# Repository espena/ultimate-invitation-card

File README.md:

# Ultimate invitation card
Invitation card for geeks!

You will find a detailed description of this project on my blog, at [espenandersen.no/ultimate-invitation-card](https://espenandersen.no/ultimate-invitation-card/).

## Prototype

## Schematics

## Development

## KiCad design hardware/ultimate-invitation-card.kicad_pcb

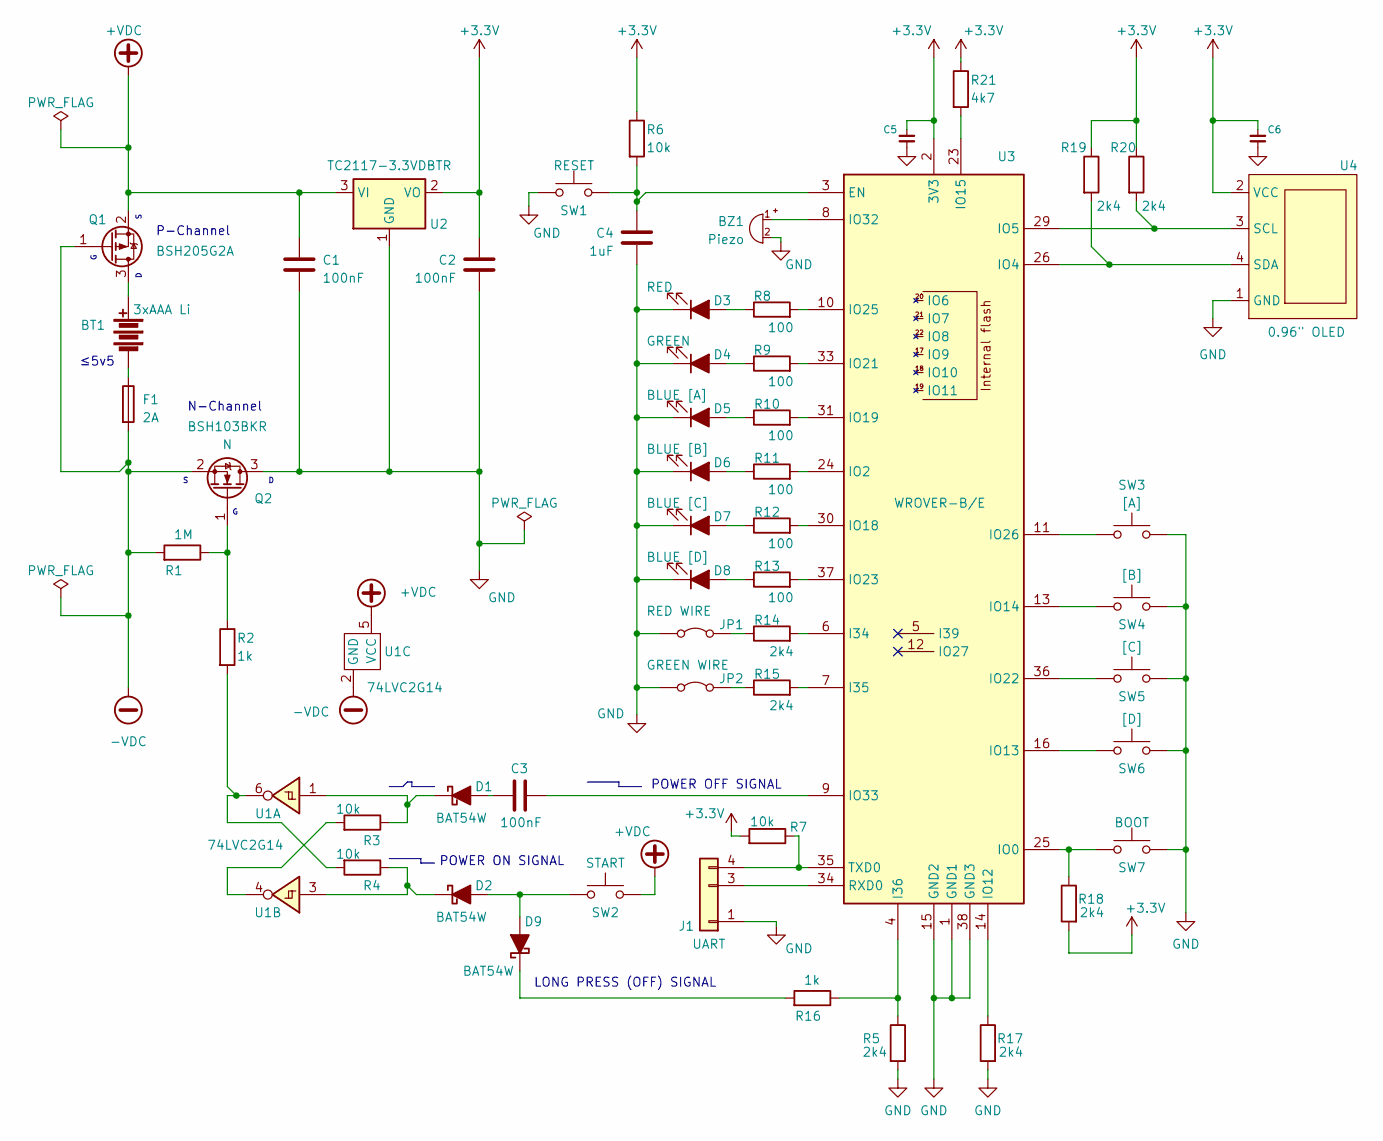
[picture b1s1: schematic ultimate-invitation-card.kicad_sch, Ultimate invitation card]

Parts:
BT1: 3xAAA Li; BatteryHolder_3xAAA_THT
BZ1: Piezo; TP094003_Transducer_9x9mm
C1, C2, C3: 100nF; C_0805_2012Metric
C4: 1uF; C_0805_2012Metric
C5, C6: C_Decoupling; C_0805_2012Metric
D1, D2, D9: BAT54W; D_SOD-123
D3: RED; LED_0805_2012Metric
D4: GREEN; LED_0805_2012Metric
D5: BLUE [A]; LED_0805_2012Metric
D6: BLUE [B]; LED_0805_2012Metric
D7: BLUE [C]; LED_0805_2012Metric
D8: BLUE [D]; LED_0805_2012Metric
F1: 2A; Fuse_0603_1608Metric
J1: UART; PinHeader_1x04_P1.27mm_Vertical_without_pin2
JP1: RED WIRE; Wire_Jumper_17.78mm
JP2: GREEN WIRE; Wire_Jumper_17.78mm
Q1: BSH205G2A; SOT-23
Q2: BSH103BKR; SOT-23
R1: 1M; R_0805_2012Metric
R2, R16: 1k; R_0805_2012Metric
R3, R4, R6, R7: 10k; R_0805_2012Metric
R5, R14, R15, R17, R18, R19, R20: 2k4; R_0805_2012Metric
R8, R9, R10, R11, R12, R13: 100; R_0805_2012Metric
R21: 4k7; R_0805_2012Metric
SW1: RESET; SW_SPST_TL3301_6x6mm_H4.3mm
SW2: START; SW_SPST_TL3301_6x6mm_H4.3mm
SW3: [A]; SW_SPST_TL3301_6x6mm_H4.3mm
SW4: [B]; SW_SPST_TL3301_6x6mm_H4.3mm
SW5: [C]; SW_SPST_TL3301_6x6mm_H4.3mm
SW6: [D]; SW_SPST_TL3301_6x6mm_H4.3mm
SW7: BOOT; SW_SPST_TL3301_6x6mm_H4.3mm
U1: 74LVC2G14; SOT-23-6
U2: TC2117-3.3VDBTR; SOT-223-3_TabPin2
U3: WROVER-B/E; ESP32-WROVER-B
U4: 0.96" OLED; OLED_SSD1306_128x64

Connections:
+3.3V: C2.1, C5.1, C6.1, R6.1, R7.2, R18.2, R19.1, R20.1, R21.1, U2.2 (VO), U3.2 (3V3), U4.2 (VCC)
+VDC: C1.1, Q1.2 (S), SW2.2, U1.5 (VCC), U2.3 (VI)
-VDC: F1.2, Q1.1 (G), Q2.2 (S), R1.2, U1.2 (GND)
GND: BZ1.2 (+), C1.2, C2.2, C4.2, C5.2, C6.2, D3.1 (K), D4.1 (K), D5.1 (K), D6.1 (K), D7.1 (K), D8.1 (K), J1.1, JP1.1 (A), JP2.1 (A), Q2.3 (D), R5.2, R17.2, SW1.2, SW3.2, SW4.2, SW5.2, SW6.2, SW7.2, U2.1 (GND), U3.1 (GND1), U3.15 (GND2), U3.38 (GND3), U4.1 (GND)
unnamed: BT1.1 (+), Q1.3 (D)
unnamed: BT1.2 (-), F1.1
unnamed: BZ1.1 (-), U3.8 (IO32)
unnamed: C3.1, D1.2 (A)
unnamed: D1.1 (K), R3.1, U1.1
unnamed: D2.2 (A), D9.2 (A), SW2.1
unnamed: D2.1 (K), R4.1, U1.3
unnamed: D3.2 (A), R8.1
unnamed: D4.2 (A), R9.1
unnamed: D5.2 (A), R10.1
unnamed: D6.2 (A), R11.1
unnamed: D7.2 (A), R12.1
unnamed: D8.2 (A), R13.1
unnamed: D9.1 (K), R16.2
unnamed: J1.3, U3.34 (RXD0)
unnamed: J1.4, R7.1, U3.35 (TXD0)
unnamed: JP1.2 (B), R14.1
unnamed: JP2.2 (B), R15.1
unnamed: Q2.1 (G), R1.1, R2.1
unnamed: R2.2, R4.2, U1.6
unnamed: R3.2, U1.4
unnamed: C4.1, R6.2, SW1.1, U3.3 (EN)
unnamed: R14.2, U3.6 (I34)
unnamed: R15.2, U3.7 (I35)
unnamed: R5.1, R16.1, U3.4 (I36)
unnamed: R18.1, SW7.1, U3.25 (IO0)
unnamed: R11.2, U3.24 (IO2)
unnamed: R19.2, U3.26 (IO4), U4.4 (SDA)
unnamed: R20.2, U3.29 (IO5), U4.3 (SCL)
unnamed: R17.1, U3.14 (IO12)
unnamed: SW6.1, U3.16 (IO13)
unnamed: SW4.1, U3.13 (IO14)
unnamed: R21.2, U3.23 (IO15)
unnamed: R12.2, U3.30 (IO18)
unnamed: R10.2, U3.31 (IO19)
unnamed: R9.2, U3.33 (IO21)
unnamed: SW5.1, U3.36 (IO22)
unnamed: R13.2, U3.37 (IO23)
unnamed: R8.2, U3.10 (IO25)
unnamed: SW3.1, U3.11 (IO26)
unnamed: C3.2, U3.9 (IO33)

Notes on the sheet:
≤5v5
LONG PRESS (OFF) SIGNAL
POWER ON SIGNAL
P-Channel
N-Channel
POWER OFF SIGNAL

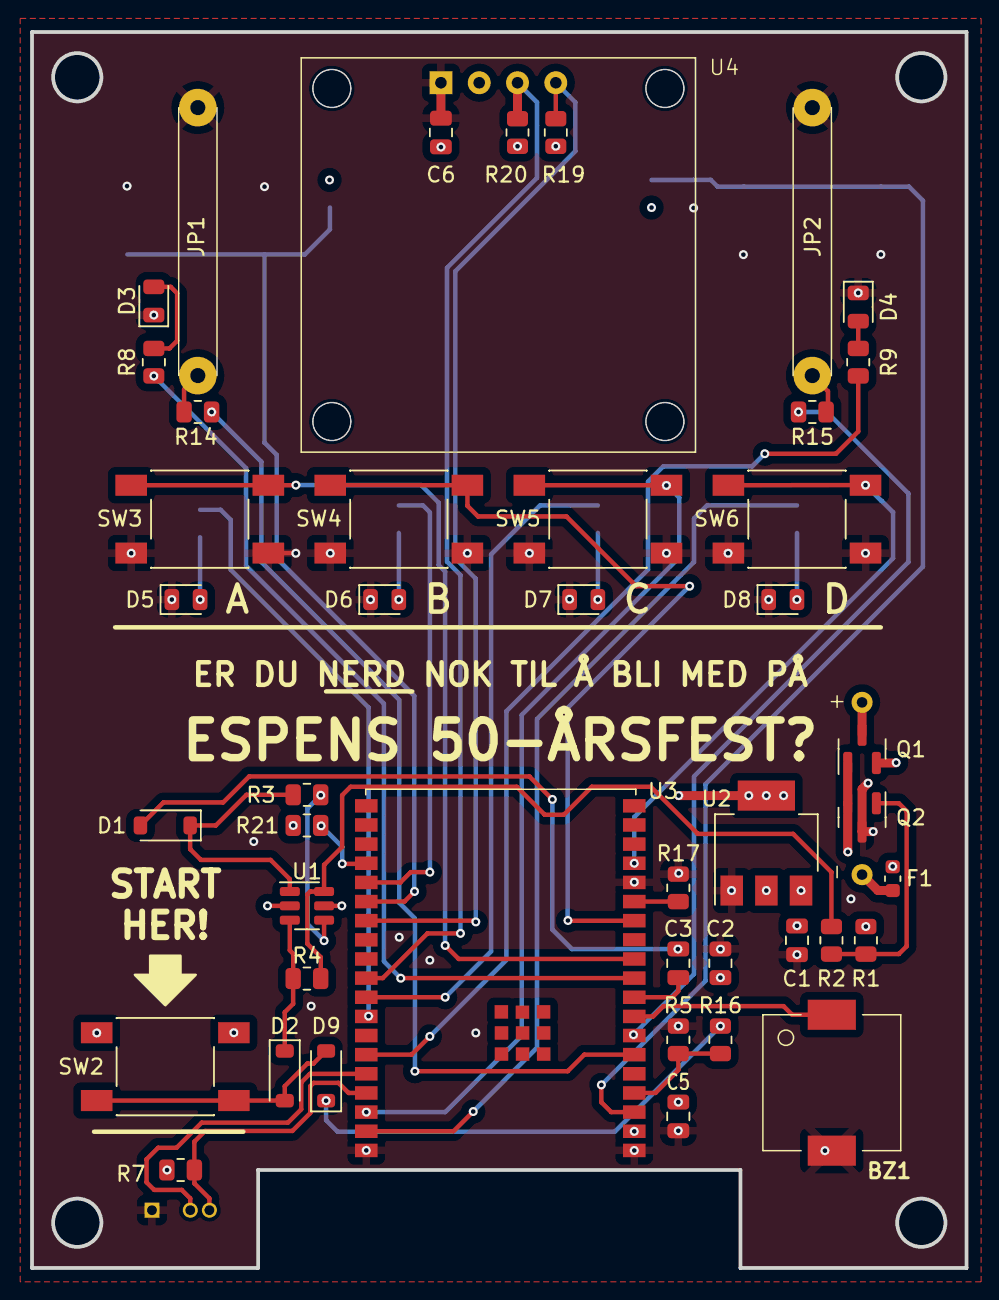
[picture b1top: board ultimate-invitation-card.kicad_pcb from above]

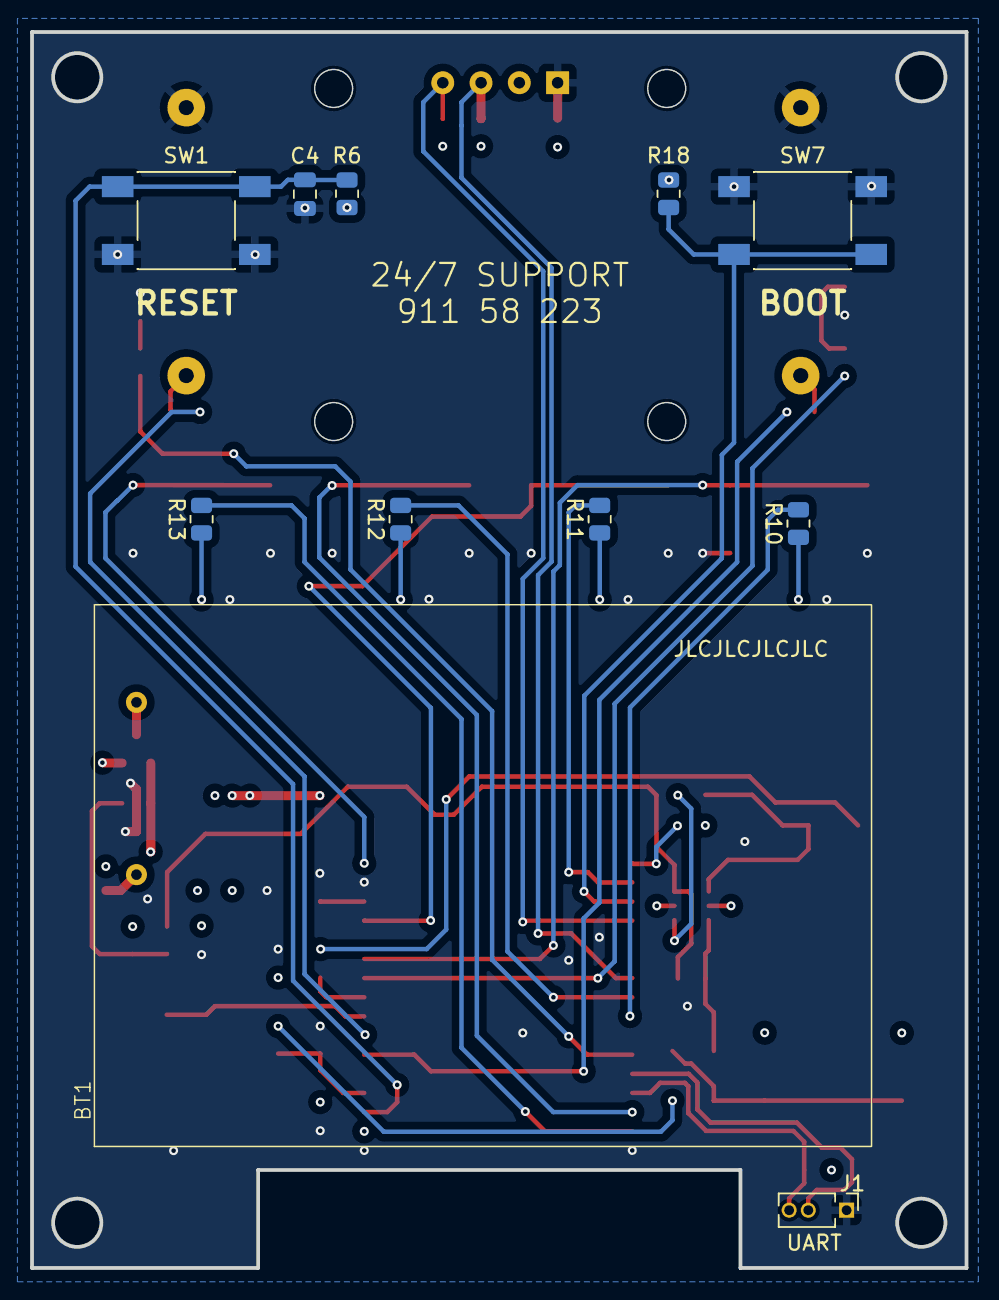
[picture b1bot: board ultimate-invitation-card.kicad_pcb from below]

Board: 4 copper layers, 62.0 x 82.0 mm, 55 parts (11 on the bottom side), 45 nets.

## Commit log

2024-03-15 Initial commit, public version
2024-03-27 Update README.md
    Add link to blog posting.
2024-03-27 Update README.md
    Fix syntax
